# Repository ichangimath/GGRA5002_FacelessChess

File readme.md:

# Faceless Chess
## Project by Kashfia Arif, Kevin Ilango, and Prayag Ichangimath

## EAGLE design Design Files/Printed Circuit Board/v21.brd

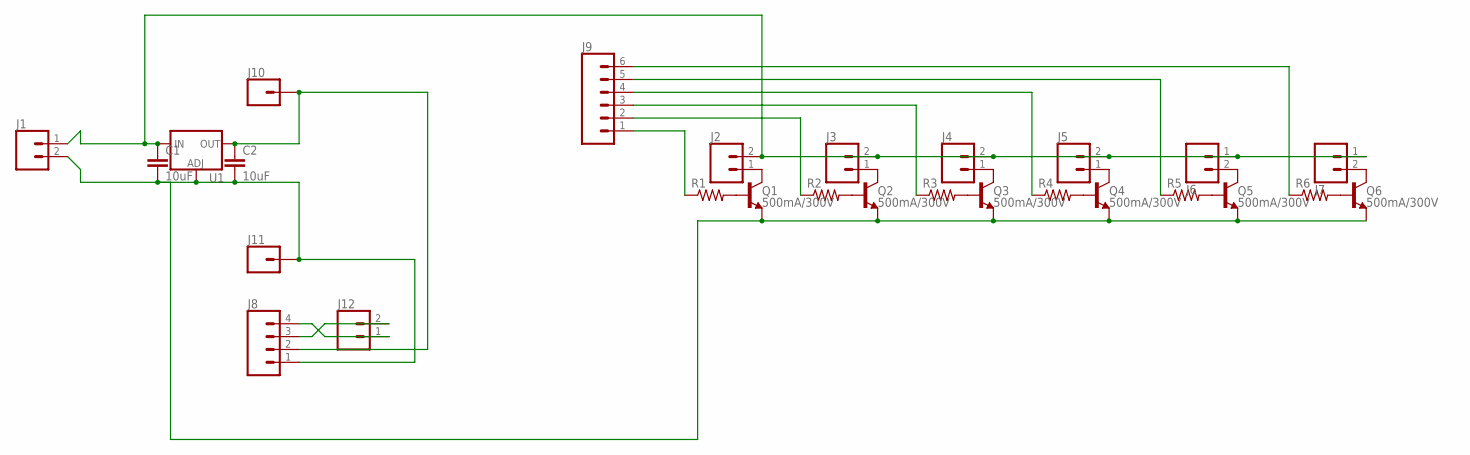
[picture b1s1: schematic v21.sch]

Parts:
C1, C2: 10uF; 1206
J1: CONN_02-JST-2MM-SMT; JST-2-SMD
J2, J3, J4, J5, J6, J7: CONN_02; 1X02
J8: CONN_04PTH; 1X04
J9: CONN_06LONGPADS; 1X06_LONGPADS
J10, J11: CONN_01PTH_LONGPAD; 1X01_LONGPAD
J12: CONN_02LOCK_LONGPADS; 1X02_LOCK_LONGPADS
Q1, Q2, Q3, Q4, Q5, Q6: 500mA/300V; SOT23-3
R1, R2, R3, R4, R5, R6: R-US_R1206; R1206
U1: V_REG_LM1117SOT223; SOT223

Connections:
unnamed: J8.3, J12.2
unnamed: C2.1, J8.2, J10.1, U1.2 (OUT), U1.4 (OUT)
unnamed: J8.4, J12.1
unnamed: J2.1, Q1.3 (C)
unnamed: Q1.1 (B), R1.2
unnamed: J3.1, Q2.3 (C)
unnamed: Q2.1 (B), R2.2
unnamed: J4.1, Q3.3 (C)
unnamed: Q3.1 (B), R3.2
unnamed: J9.1, R1.1
unnamed: J5.1, Q4.3 (C)
unnamed: Q4.1 (B), R4.2
unnamed: J6.2, Q5.3 (C)
unnamed: Q5.1 (B), R5.2
unnamed: J7.2, Q6.3 (C)
unnamed: Q6.1 (B), R6.2
unnamed: C1.1, J1.1 (2), J2.2, J3.2, J4.2, J5.2, J6.1, J7.1, U1.3 (IN)
unnamed: C1.2, C2.2, J1.2 (1), J8.1, J11.1, Q1.2 (E), Q2.2 (E), Q3.2 (E), Q4.2 (E), Q5.2 (E), Q6.2 (E), U1.1 (ADJ)
unnamed: J9.2, R2.1
unnamed: J9.3, R3.1
unnamed: J9.4, R4.1
unnamed: J9.5, R5.1
unnamed: J9.6, R6.1

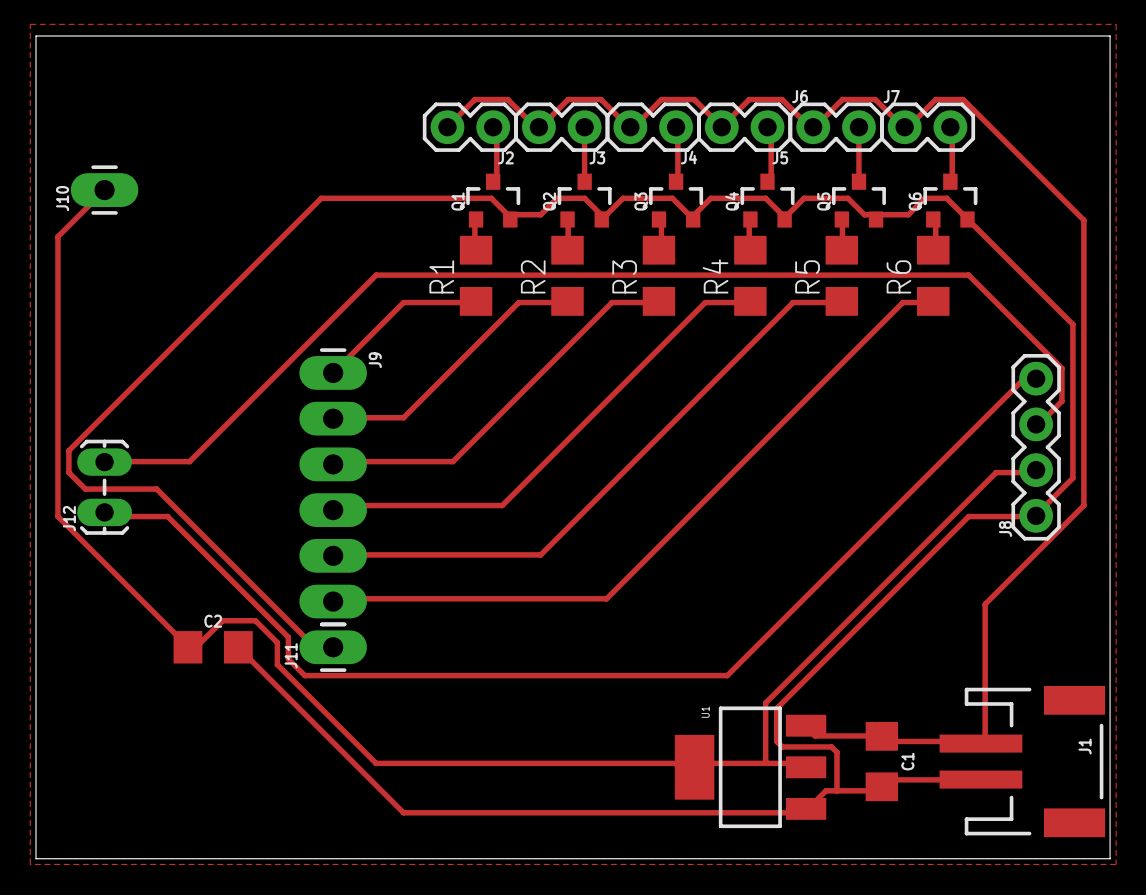
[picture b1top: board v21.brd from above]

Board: 2 copper layers, 59.7 x 45.7 mm, 27 parts (0 on the bottom side), 23 nets.

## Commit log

2022-08-05 Latest

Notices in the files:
parts and their libraries:
SparkFun-Capacitors: Licensing: Creative Commons ShareAlike 4.0 International - https://creativecommons.org/licenses/by-sa/4.0
